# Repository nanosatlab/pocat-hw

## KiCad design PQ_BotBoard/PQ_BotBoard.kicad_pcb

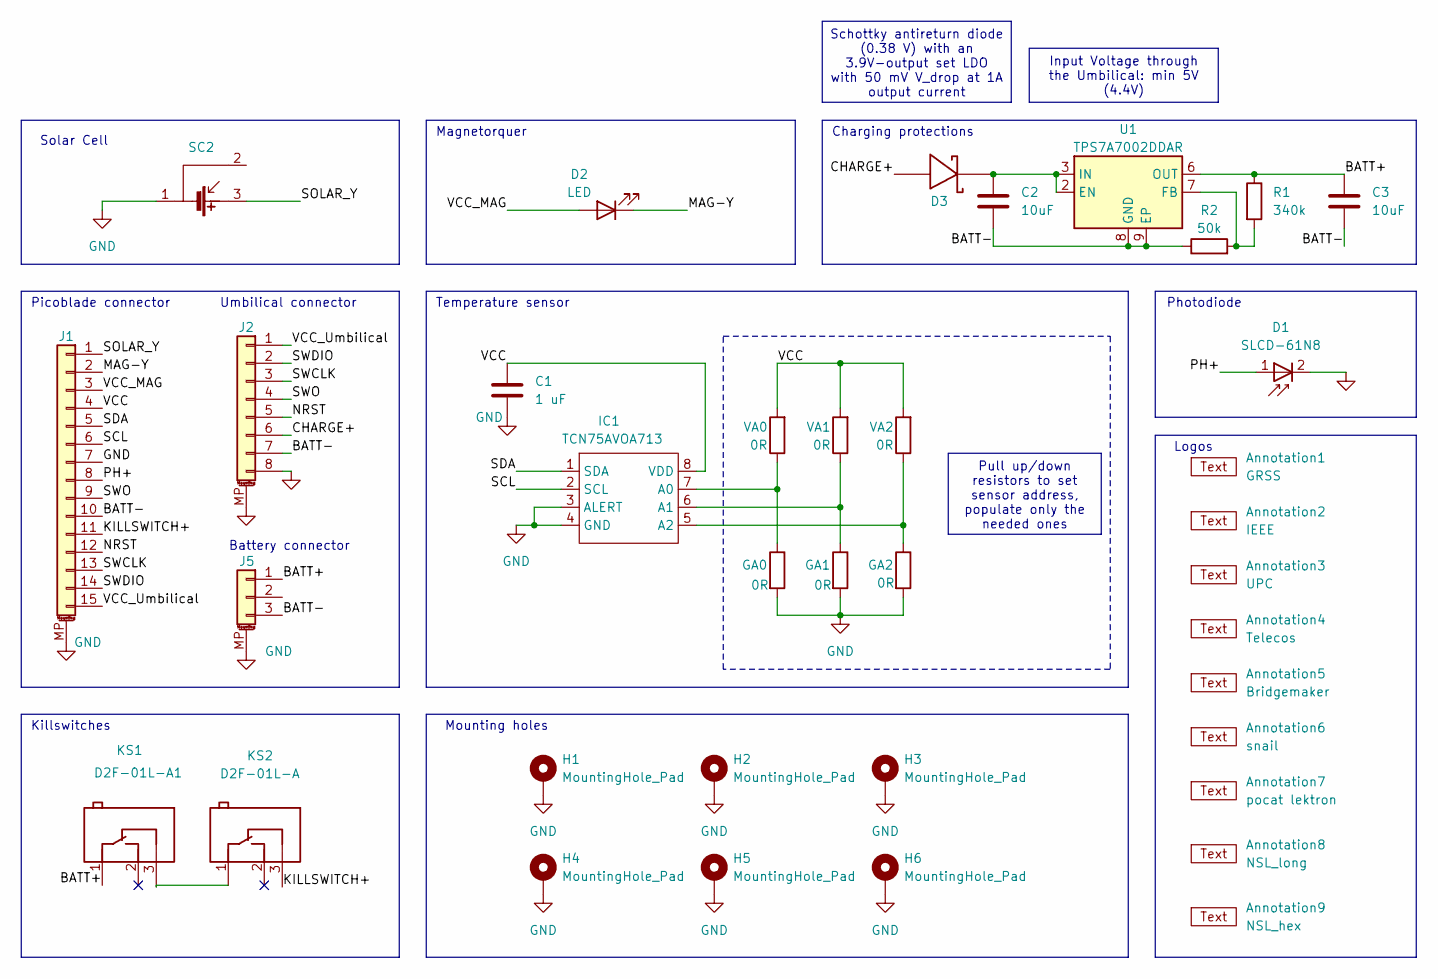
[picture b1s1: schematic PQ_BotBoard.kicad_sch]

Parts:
Annotation1: GRSS
Annotation2: IEEE; IEEE_logo
Annotation3: UPC; UPC_positiu
Annotation4: Telecos
Annotation5: Bridgemaker
Annotation6: snail; Snail
Annotation7: pocat lektron; pocat-lektron
Annotation8: NSL_long; NSL-small
Annotation9: NSL_hex; NSL_hexagon
C1: 1 uF; C_0603_1608Metric; Manufacturer Part Numbe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 GRM188R72A104KA35J
C2, C3: 10uF; C_0603_1608Metric
D1: SLCD-61N8; Manufacturer Part Numbe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 SLCD-61N8
D2: LED; LED_0402_1005Metric
D3: RBS1LAM40ATR_Schottky
GA0, GA1, GA2: 0R; R_0805_2012Metric; Manufacturer Part Numbe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 CRCW08055K00JNTA
H1, H2, H3, H4, H5, H6: MountingHole_Pad; MountingHole_2.2mm_M2_Pad; Manufacturer Part Numbe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 N/A
IC1: TCN75AVOA713; TCN75AVOA; Manufacturer Part Numbe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 TCN75AVOA
J1: 53261-1471; Molex_PicoBlade_53261-1571_1x15-1MP_P1.25mm_Horizontal; Manufacturer Part Numbe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 PicoBlade_53261-1571
J2: Conn_01x08_MountingPin; Molex_PicoBlade_53398-0871_1x08-1MP_P1.25mm_Vertical; Manufacturer Part Numbe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 PicoBlade_53398-0871
J5: Conn_01x03_MountingPin; Molex_PicoBlade_53261-0371_1x03-1MP_P1.25mm_Horizontal
KS1: D2F-01L-A1; D2FLA1; Manufacturer Part Numbe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 D2F-01L
KS2: D2F-01L-A; D2FLA; Manufacturer Part Numbe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 D2F-01L-A
R1: 340k; R_0603_1608Metric
R2: 50k; R_0603_1608Metric
SC2: Lighttricity_S3040_CIC
U1: TPS7A7002DDAR; TI_SO-PowerPAD-8
VA0, VA1, VA2: 0R; R_0805_2012Metric; Manufacturer Part Numbe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 CRCW08055K00JNTA

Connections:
/BATT+: C3.1, J5.1, KS1.1 (COM), R1.1, U1.6 (OUT)
/BATT-: C2.2, C3.2, J1.10, J2.7, J5.3, R2.1, U1.8 (GND), U1.9 (EP)
/CHARGE+: D3.2, J2.6
/KILLSWITCH+: J1.11, KS2.3 (NC)
/MAG-Y: D2.1 (K), J1.2
/NRST: J1.12, J2.5
/PH+: D1.1, J1.8
/SCL: IC1.2 (SCL), J1.6
/SDA: IC1.1 (SDA), J1.5
/SOLAR_Y: J1.1, SC2.3
/SWCLK: J1.13, J2.3
/SWDIO: J1.14, J2.2
/SWO: J1.9, J2.4
/VCC: C1.1, IC1.8 (VDD), J1.4, VA0.2, VA1.2, VA2.2
/VCC_MAG: D2.2 (A), J1.3
/VCC_Umbilical: J1.15, J2.1
GND: C1.2, D1.2, GA0.2, GA1.2, GA2.2, H1.1, H2.1, H3.1, H4.1, H5.1, H6.1, IC1.3 (ALERT), IC1.4 (GND), J1.7, J1.MP (MountPin), J2.8, J2.MP (MountPin), J5.MP (MountPin), SC2.1
unnamed: GA0.1, IC1.7 (A0), VA0.1
unnamed: GA1.1, IC1.6 (A1), VA1.1
unnamed: GA2.1, IC1.5 (A2), VA2.1
unnamed: KS1.3 (NC), KS2.1 (COM)
unnamed: C2.1, D3.1, U1.2 (EN), U1.3 (IN)
unnamed: R1.2, R2.2, U1.7 (FB)

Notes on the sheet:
Input Voltage through the Umbilical: min 5V (4.4V)
Schottky antireturn diode (0.38 V) with an 3.9V-output set LDO with 50 mV V_drop at 1A output current
Pull up/down resistors to set sensor address, populate only the needed ones
Temperature sensor
Killswitches
Mounting holes
Solar Cell
Magnetorquer
Charging protections
Photodiode
Umbilical connector
Battery connector
Picoblade connector
Logos

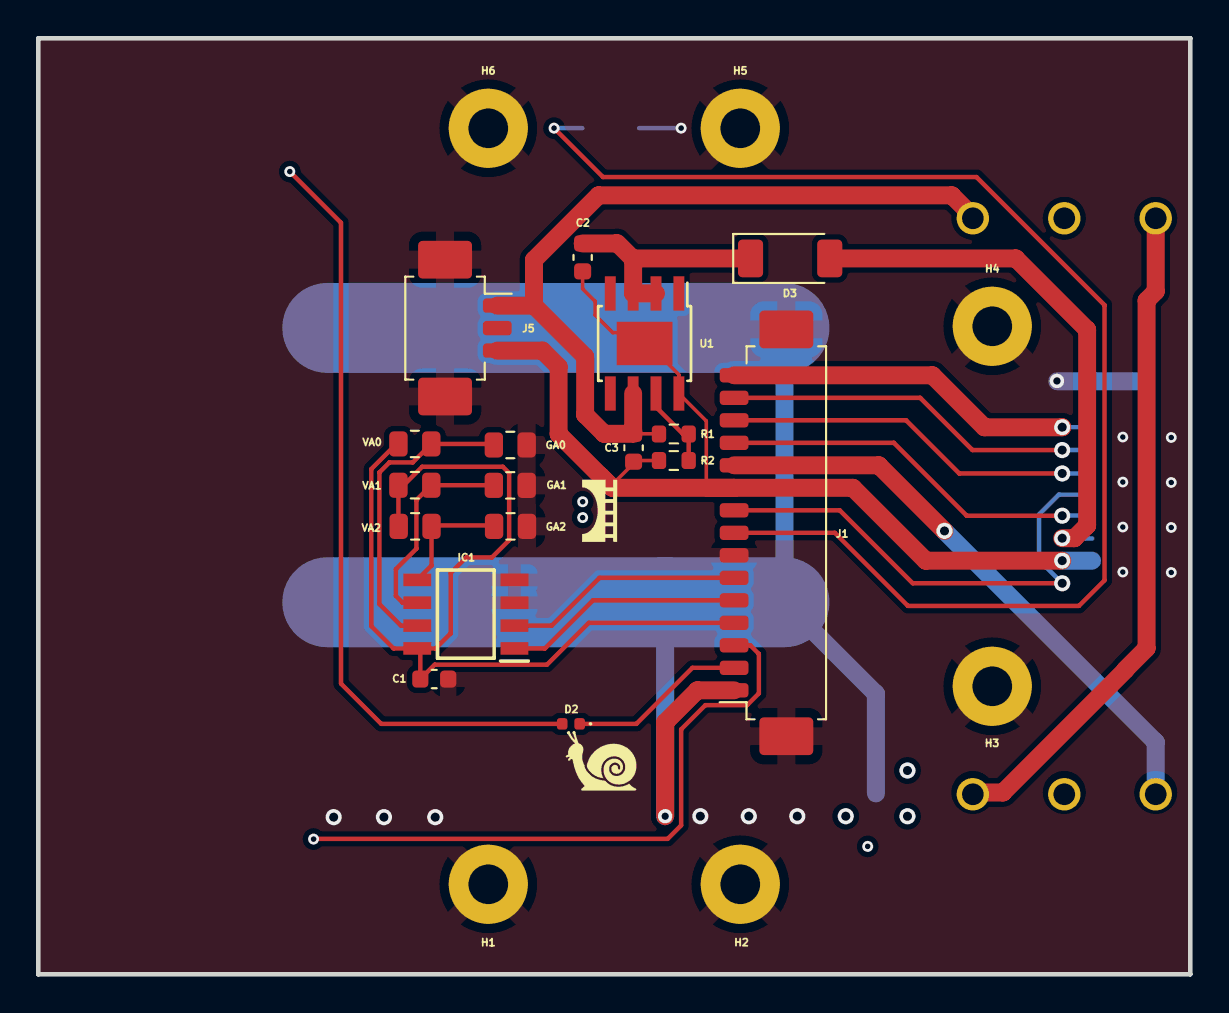
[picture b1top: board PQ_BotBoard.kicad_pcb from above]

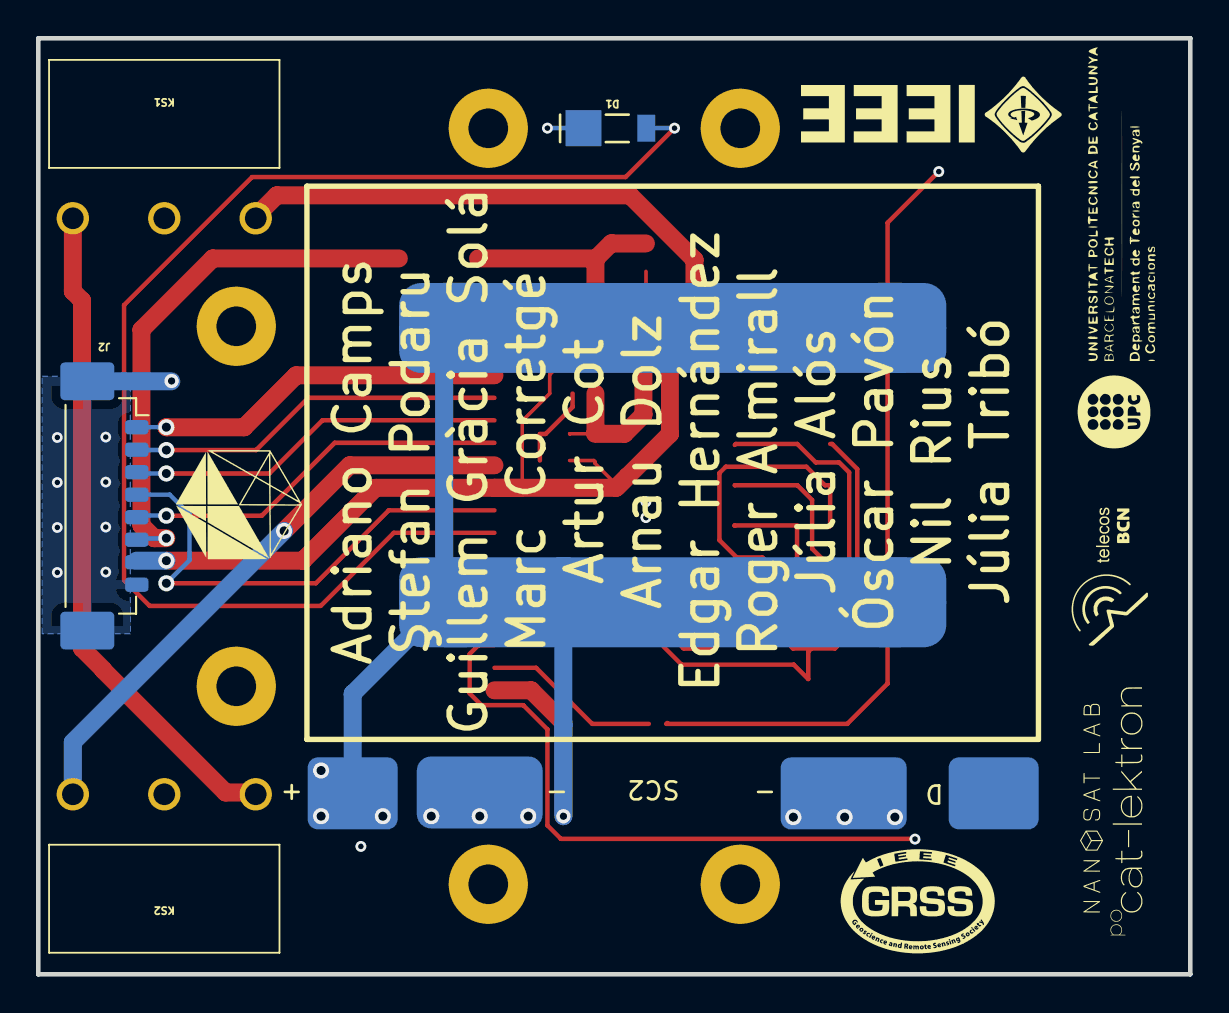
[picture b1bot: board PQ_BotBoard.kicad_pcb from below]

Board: 6 copper layers, 64.0 x 52.0 mm, 37 parts (12 on the bottom side), 23 nets.

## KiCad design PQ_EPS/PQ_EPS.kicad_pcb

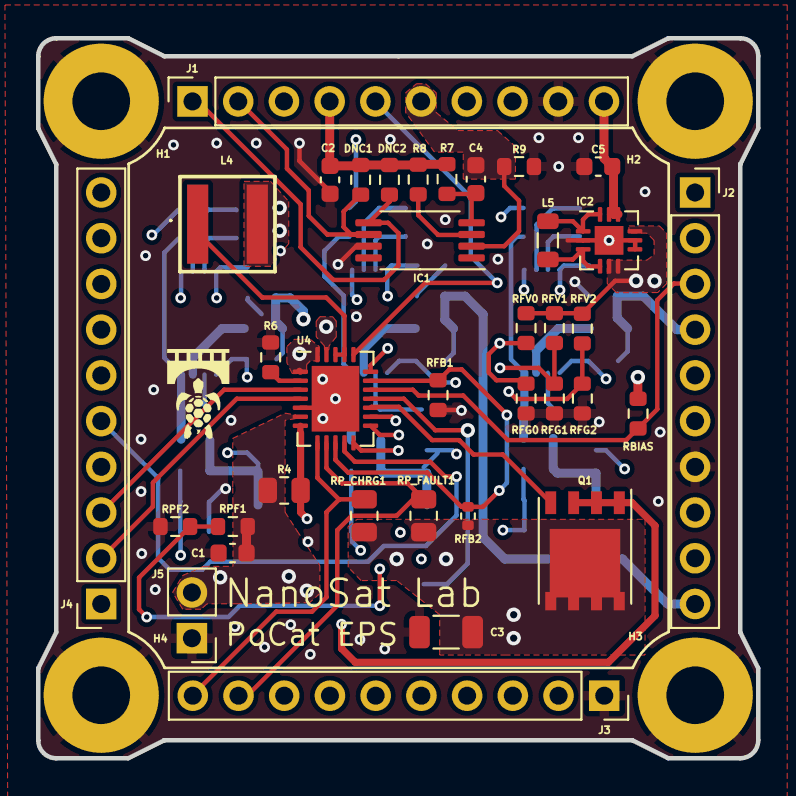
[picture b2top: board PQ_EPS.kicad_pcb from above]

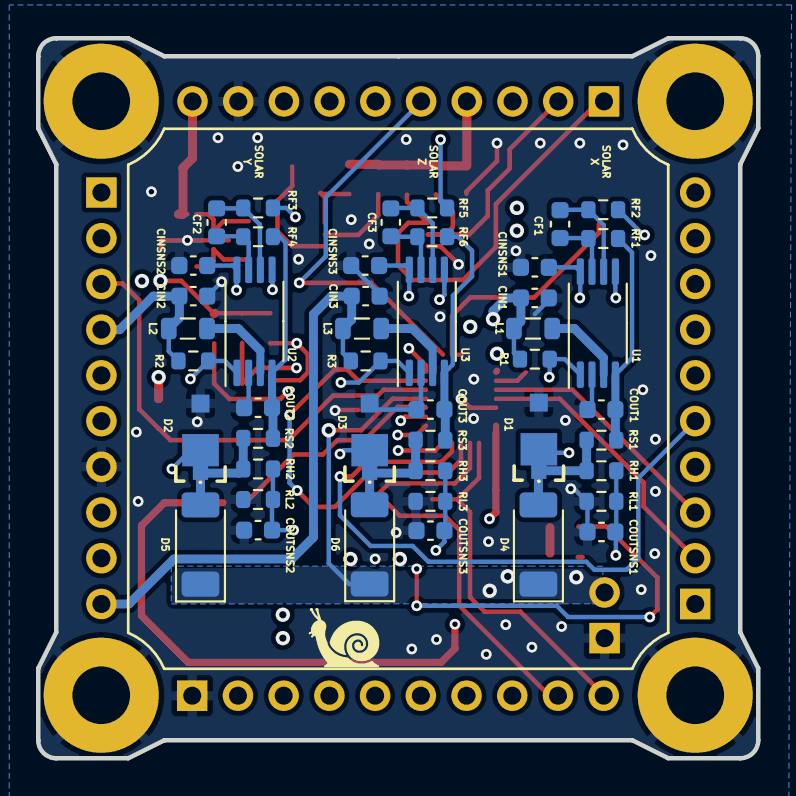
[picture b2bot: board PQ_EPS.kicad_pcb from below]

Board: 4 copper layers, 40.0 x 40.0 mm, 88 parts (46 on the bottom side), 52 nets.

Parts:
Annotation1: Silkscreen_Annotation; Bridgemaker
Annotation2: Silkscreen_Annotation; NakNak
Annotation3: Silkscreen_Annotation; Snail
C1: 2.2u; C_0603_1608Metric
C2: 10u; C_0603_1608Metric
C3: 100u; C_1206_3216Metric
C4: 0.1u; C_0603_1608Metric
C5: 22u; C_0603_1608Metric
CF1, CF2, CF3: 1u; C_0603_1608Metric
CIN1, CIN2, CIN3: 1.5u; C_0603_1608Metric
CINSNS1, CINSNS2, CINSNS3: 1n; C_0603_1608Metric
COUT1, COUT2, COUT3: 10u; C_0603_1608Metric
COUTSNS1, COUTSNS2, COUTSNS3: 1n; C_0603_1608Metric
D1, D2, D3: SMM4F; SMM4F15ATR
D4, D5, D6: shottky; RBS1LAM40ATR_Schottky
DNC1, DNC2: 20k; R_0603_1608Metric
H1, H2, H3, H4: MountingHole_Pad; MountingHole_3.2mm_M3_Pad
IC1: DS2782E+; TSSOP-8_4.4x3mm_P0.65mm
IC2: ISL9120IRTNZ
J1, J2, J3, J4: CES-110-02-L-S; SLW-110-01
J5: CES-102-02
L1, L2, L3: 10u; L_0805_2012Metric
L4: 2.2u; XAL5030222MEC
L5: 1u; L_0805_2012Metric
Q1: SIR424DP
R1, R2, R3, R8: 1k; R_0603_1608Metric
R4: 75m; R_0805_2012Metric
R6: 2k; R_0603_1608Metric
R7: 510; R_0603_1608Metric
R9: 15m; R_0603_1608Metric
RBIAS1: 10k; R_0603_1608Metric
RF1, RF2, RF3, RF4, RF5, RF6: 1k; R_0603_1608Metric
RFB1: 68k; R_0603_1608Metric
RFB2: 255k; R_0402_1005Metric
RFG0, RFG1, RFG2: 1k; R_0603_1608Metric
RFV0, RFV1, RFV2: 1k; R_0603_1608Metric
RH1, RH2, RH3: 910k; R_0603_1608Metric
RL1, RL2, RL3: 360k; R_0603_1608Metric
RPF1: 147k; R_0603_1608Metric
RPF2: 68k; R_0603_1608Metric
RP_CHRG1: 5k; R_0805_2012Metric
RP_FAULT1: 5k; R_0805_2012Metric
RS1, RS2, RS3: 300m; R_0603_1608Metric
U1, U2, U3: SPV1040TTR; TSSOP-8_4.4x3mm_P0.65mm
U4: LTC4040EUFD#PBF; QFN-24-1EP_4x5mm_P0.5mm_EP2.65x3.65mm

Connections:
3V3_PERM: C5.2, IC2.10 (FB), IC2.11 (VOUT), J1.10, RBIAS1.2
/F0: RFG0.1, RFV0.2, U4.14 (F0)
/F1: RFG1.1, RFV1.2, U4.13 (F1)
/F2: RFG2.1, RFV2.2, U4.12 (F2)
/PROG: R6.2, U4.2 (PROG)
BATT-: C4.2, IC1.2 (VSS), J1.6, R9.1
BATT_NTC: J2.3, RBIAS1.1, U4.17 (NTC)
CHOUT: C3.1, IC2.5 (VIN_1), IC2.6 (VIN_2), IC2.9 (EN), Q1.5 (D), RFB2.2, RFV0.1, RFV1.1, RFV2.1, RP_CHRG1.1, RP_FAULT1.1, U4.1 (VSYS), U4.24 (VSYS)
CHRG: J3.10, RP_CHRG1.2, U4.8 (CHRG#)
CHRGOFF: J4.2, U4.4 (CHGOFF)
CLPROG: J4.3, U4.3 (CLPROG)
FAULT: J3.9, RP_FAULT1.2, U4.9 (FAULT#)
GND: C1.2, C2.2, C3.2, C5.1, CIN1.1, CIN2.1, CIN3.1, CINSNS1.1, CINSNS2.1, CINSNS3.1, COUT1.1, COUT2.1, COUT3.1, COUTSNS1.1, COUTSNS2.1, COUTSNS3.1, D1.2, D2.2, D3.2, H1.1, H2.1, H3.1, H4.1, IC1.7 (SNS), IC2.2 (PGND), IC2.7 (BYPS), IC2.8 (GND), IC2.13 (EP), J1.9, J2.7, J3.1, J5.1, R6.1, R9.2, RFB1.2, RFG0.2, RFG1.2, RFG2.2, RL1.2, RL2.2, RL3.2, RPF2.1, U1.2 (GND), U2.2 (GND), U3.2 (GND), U4.5 (BSTOFF), U4.25 (EPAD)
KILLSWITCH+: C2.1, DNC1.2, DNC2.2, J1.4, L4.2, R7.2, R8.2, U4.23 (BAT)
NRST: J4.5, U4.11 (RST#)
unnamed: D1.1, D4.2, RF2.2, RH1.1, RS1.2
unnamed: D2.1, D5.2, RF3.2, RH2.1, RS2.2
unnamed: D3.1, D6.2, RF5.2, RH3.1, RS3.2
unnamed: C4.1, IC1.4 (VDD), R7.1
unnamed: IC1.3 (VIN), R8.1
unnamed: IC2.3 (LX1_1), IC2.4 (LX1_2), L5.1
unnamed: IC2.1 (LX2_1), IC2.12 (LX2_2), L5.2
unnamed: L4.1, U4.21 (SW), U4.22 (SW)
unnamed: Q1.4 (G), U4.15 (IGATE)
unnamed: CF1.1, RF2.1, U1.6 (ICTRL-MINUS)
unnamed: CF1.2, RF1.1, U1.7 (ICTRL-PLUS)
unnamed: L1.1, U1.3 (LX)
unnamed: CINSNS1.2, R1.1, U1.1 (MPP-SET), U1.8 (XSHUT)
unnamed: COUTSNS1.2, RH1.2, RL1.1, U1.5 (VCTRL)
unnamed: COUT1.2, RF1.2, RS1.1, U1.4 (VOUT)
unnamed: CF2.1, RF3.1, U2.6 (ICTRL-MINUS)
unnamed: CF2.2, RF4.1, U2.7 (ICTRL-PLUS)
unnamed: L2.2, U2.3 (LX)
unnamed: CINSNS2.2, R2.1, U2.1 (MPP-SET), U2.8 (XSHUT)
unnamed: COUTSNS2.2, RH2.2, RL2.1, U2.5 (VCTRL)
unnamed: COUT2.2, RF4.2, RS2.1, U2.4 (VOUT)
unnamed: CF3.1, RF5.1, U3.6 (ICTRL-MINUS)
unnamed: CF3.2, RF6.1, U3.7 (ICTRL-PLUS)
unnamed: L3.2, U3.3 (LX)
unnamed: CINSNS3.2, R3.1, U3.1 (MPP-SET), U3.8 (XSHUT)
unnamed: COUTSNS3.2, RH3.2, RL3.1, U3.5 (VCTRL)
unnamed: COUT3.2, RF6.2, RS3.1, U3.4 (VOUT)
unnamed: RFB1.1, RFB2.1, U4.10 (RSTFB), U4.18 (BSTFB)
unnamed: Q1.1 (S), Q1.2 (S), Q1.3 (S), R4.2, U4.7 (CLN)
unnamed: RPF1.1, RPF2.2, U4.19 (PFI)
OVSNS: C1.1, D4.1, D5.1, D6.1, J5.2, R4.1, RPF1.2, U4.6 (VIN), U4.16 (OVSNS)
PFO: J1.5, U4.20 (PF0#)
SCL1: DNC1.1, IC1.6 (SCL), J1.2
SDA1: DNC2.1, IC1.5 (SDA), J1.1
SOLAR_X: CIN1.2, J4.1, L1.2, R1.2
SOLAR_Y: CIN2.2, J2.4, L2.1, R2.2
SOLAR_Z: CIN3.2, J2.10, L3.1, R3.2

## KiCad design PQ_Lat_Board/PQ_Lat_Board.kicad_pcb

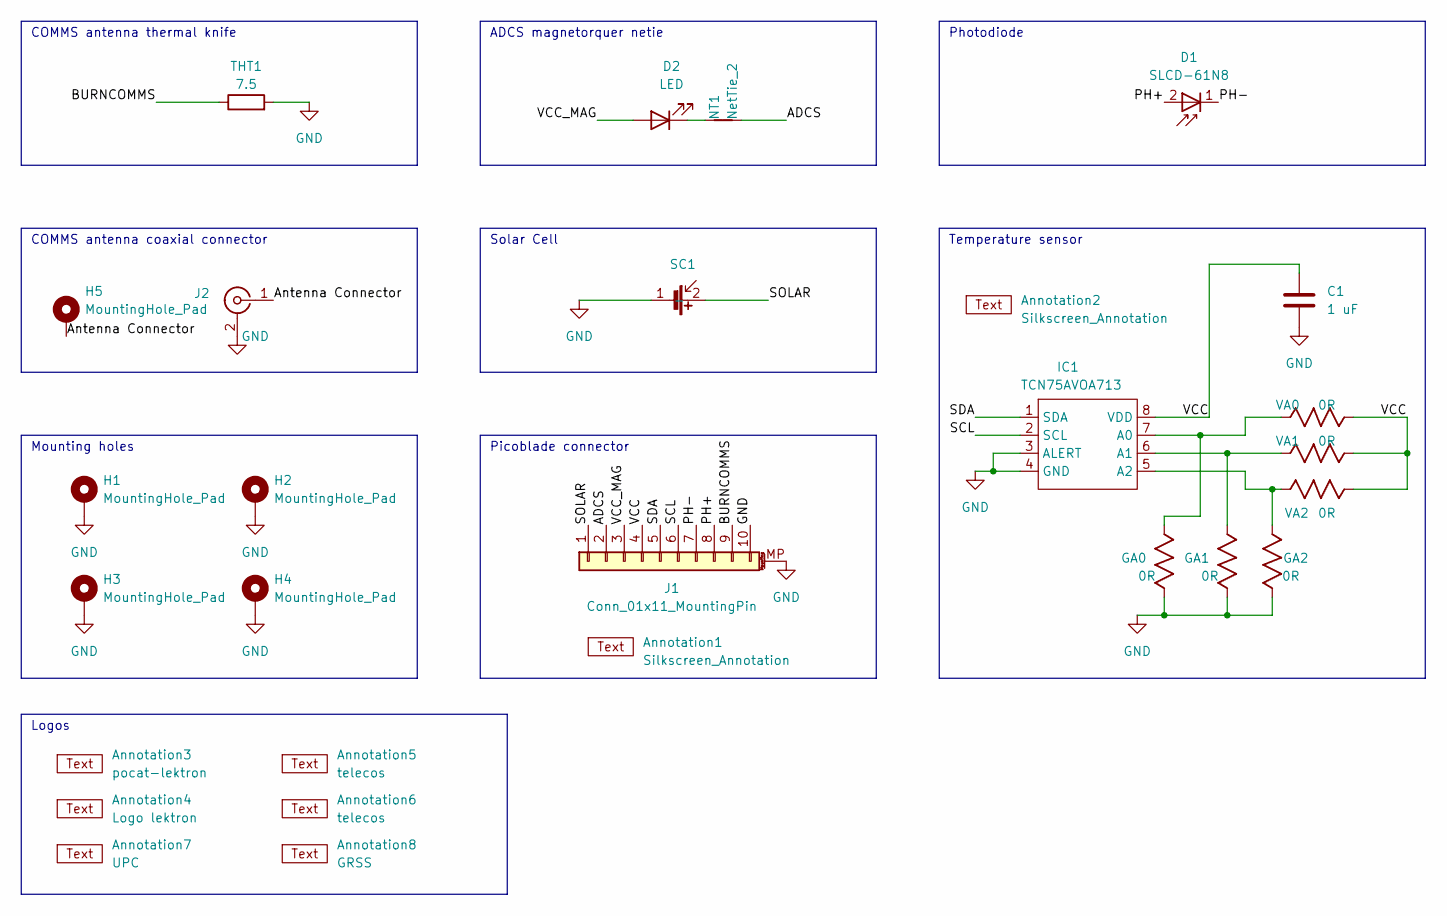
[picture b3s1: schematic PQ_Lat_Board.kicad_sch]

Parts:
Annotation1: Silkscreen_Annotation; Bridgemaker
Annotation2: Silkscreen_Annotation; snail
Annotation3: pocat-lektron
Annotation4: Logo lektron; logo_pq
Annotation5: telecos; Telecos
Annotation6: telecos; NSL-small
Annotation7: UPC; UPC_small
Annotation8: GRSS
C1: 1 uF; C_0603_1608Metric; Manufacturer Part Numbe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 GRM188R72A104KA35J
D1: SLCD-61N8; Manufacturer Part Numbe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 SLCD-61N8
D2: LED; LED_0402_1005Metric
GA0, GA1, GA2: 0R; R_0805_2012Metric; Manufacturer Part Numbe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 CRCW08055K00JNTA
H1, H2, H3, H4: MountingHole_Pad; MountingHole_2.2mm_M2_Pad; Manufacturer Part Numbe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 N/A
H5: MountingHole_Pad; MountingHole_2.2mm_M2_DIN965_Pad_TopOnly; Manufacturer Part Numbe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 N/A
IC1: TCN75AVOA713; TCN75AVOA; Manufacturer Part Numbe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 TCN75AVOA
J1: Conn_01x11_MountingPin; Molex_PicoBlade_53261-1071_1x10-1MP_P1.25mm_Horizontal; Manufacturer Part Numbe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 PicoBlade_53261
J2: Conn_Coaxial; U.FL_Hirose_U.FL-R-SMT-1_Vertical
NT1: NetTie_2; NetTie-2_SMD_Pad0.5mm; Manufacturer Part Numbe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 N/A
SC1: Lighttricity_S3040_CIC
THT1: 7.5; R_Axial_DIN0309_L9.0mm_D3.2mm_P12.70mm_Horizontal; Manufacturer Part Numbe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 MRS25000C7508FCT00
VA0, VA1, VA2: 0R; R_0805_2012Metric; Manufacturer Part Numbe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 CRCW08055K00JNTA

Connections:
/ADCS: J1.2, NT1.2
/Antenna Connector: H5.1, J2.1 (In)
/BURNCOMMS: J1.9, THT1.1
/PH+: D1.2, J1.8
/PH-: D1.1, J1.7
/SCL: IC1.2 (SCL), J1.6
/SDA: IC1.1 (SDA), J1.5
/SOLAR: J1.1, SC1.2
/VCC: C1.1, IC1.8 (VDD), J1.4, VA0.2, VA1.2, VA2.2
/VCC_MAG: D2.2 (A), J1.3
GND: C1.2, GA0.1, GA1.1, GA2.1, H1.1, H2.1, H3.1, H4.1, IC1.3 (ALERT), IC1.4 (GND), J1.10, J1.MP (MountPin), J2.2 (Ext), SC1.1 (-), THT1.2
unnamed: D2.1 (K), NT1.1
unnamed: GA0.2, IC1.7 (A0), VA0.1
unnamed: GA1.2, IC1.6 (A1), VA1.1
unnamed: GA2.2, IC1.5 (A2), VA2.1

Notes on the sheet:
COMMS antenna thermal knife
Temperature sensor
Mounting holes
COMMS antenna coaxial connector
Solar Cell
Logos
Photodiode
ADCS magnetorquer netie
Picoblade connector

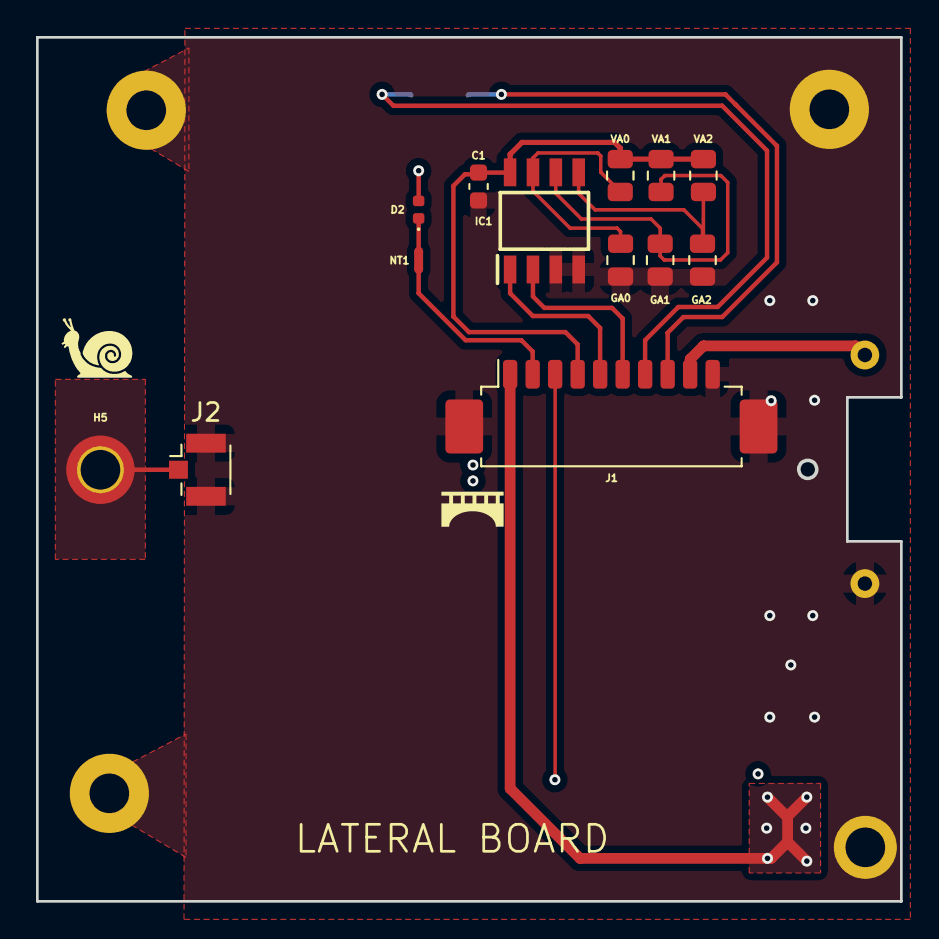
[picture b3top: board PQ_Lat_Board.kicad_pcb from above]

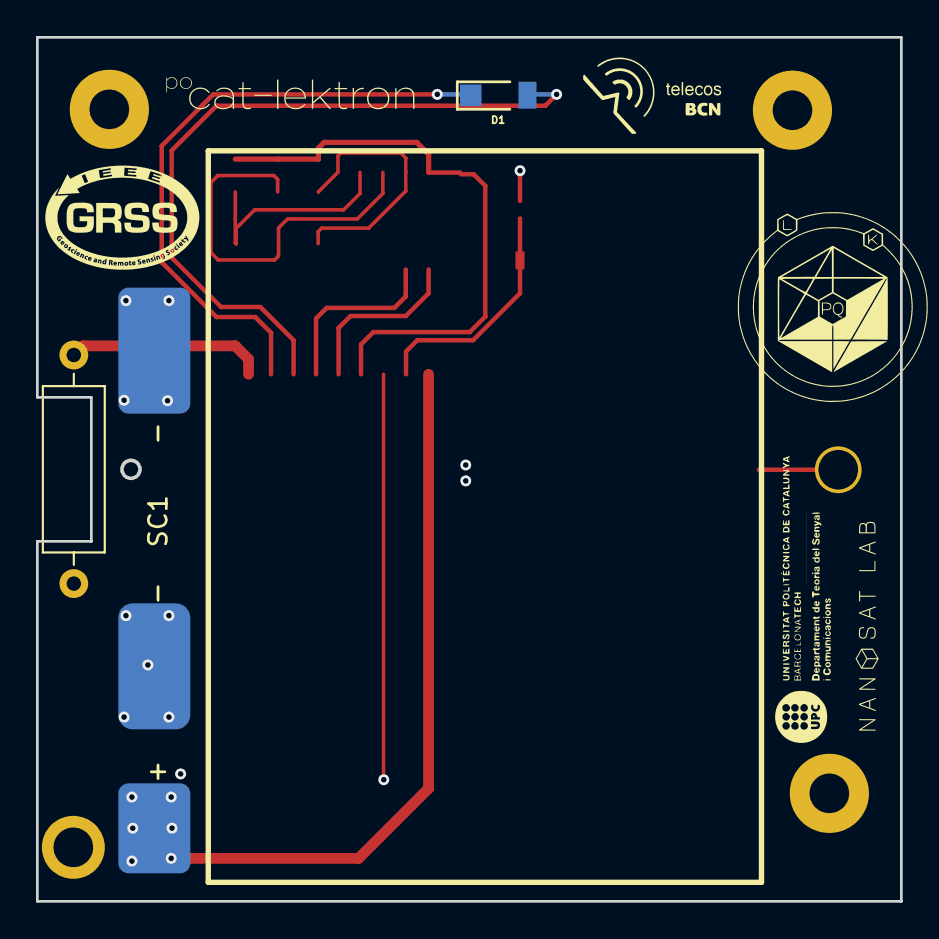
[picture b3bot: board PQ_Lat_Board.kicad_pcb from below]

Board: 6 copper layers, 48.0 x 48.0 mm, 28 parts (9 on the bottom side), 15 nets.

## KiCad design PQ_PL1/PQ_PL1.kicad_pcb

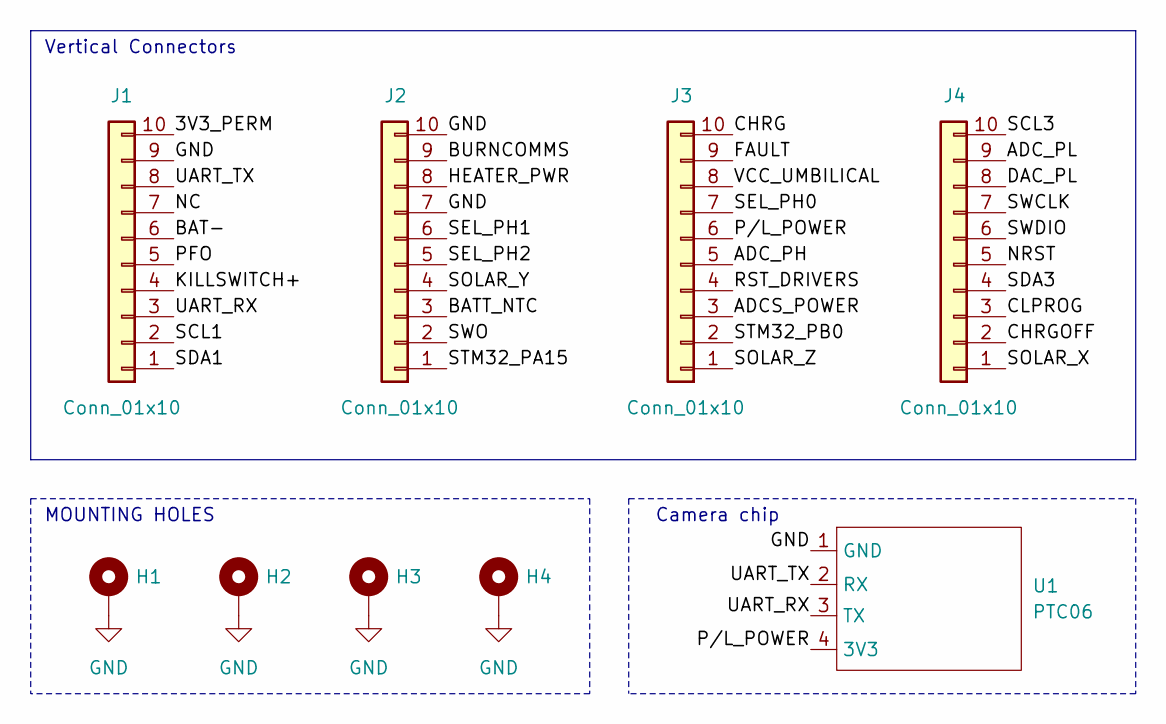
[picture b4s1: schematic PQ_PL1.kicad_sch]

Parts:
H1, H2, H3, H4: MountingHole_Pad; MountingHole_3.2mm_M3_Pad
J1, J2, J3, J4: Conn_01x10; BBL-110-Y-X
U1: PTC06

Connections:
/3V3_PERM: J1.10
/ADCS_POWER: J3.3
/ADC_PH: J3.5
/ADC_PL: J4.9
/BAT-: J1.6
/BATT_NTC: J2.3
/BURNCOMMS: J2.9
/CHRG: J3.10
/CHRGOFF: J4.2
/CLPROG: J4.3
/DAC_PL: J4.8
/FAULT: J3.9
/HEATER_PWR: J2.8
/KILLSWITCH+: J1.4
/NC: J1.7
/NRST: J4.5
/PFO: J1.5
/P/L_POWER: J3.6, U1.4 (3V3)
/RST_DRIVERS: J3.4
/SCL1: J1.2
/SCL3: J4.10
/SDA1: J1.1
/SDA3: J4.4
/SEL_PH0: J3.7
/SEL_PH1: J2.6
/SEL_PH2: J2.5
/SOLAR_X: J4.1
/SOLAR_Y: J2.4
/SOLAR_Z: J3.1
/STM32_PA15: J2.1
/STM32_PB0: J3.2
/SWCLK: J4.7
/SWDIO: J4.6
/SWO: J2.2
/UART_RX: J1.3, U1.3 (TX)
/UART_TX: J1.8, U1.2 (RX)
/VCC_UMBILICAL: J3.8
GND: H1.1, H2.1, H3.1, H4.1, J1.9, J2.7, J2.10, U1.1 (GND)

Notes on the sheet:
MOUNTING HOLES
Camera chip
Vertical Connectors

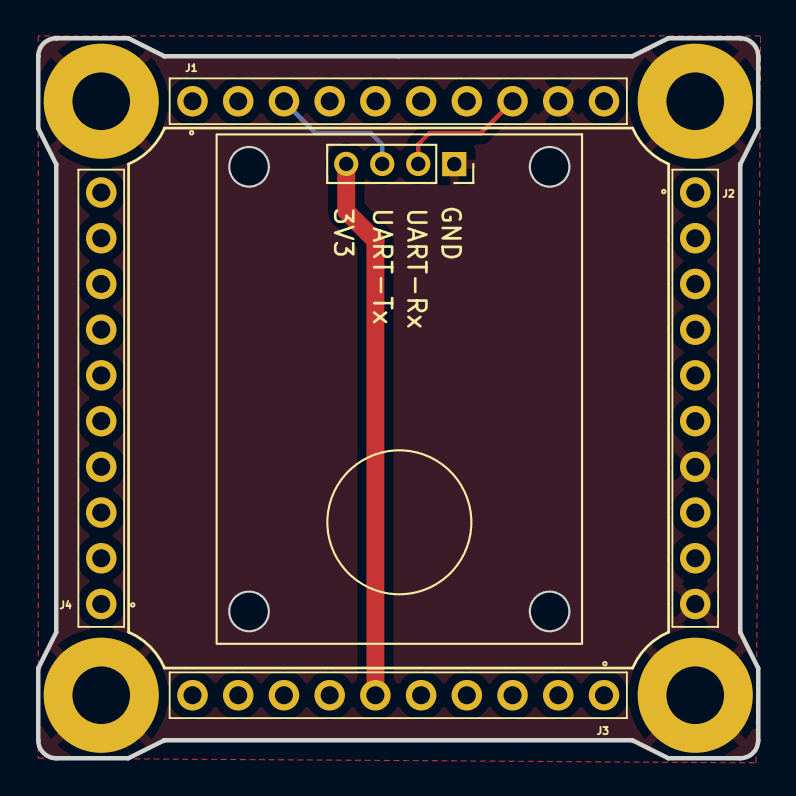
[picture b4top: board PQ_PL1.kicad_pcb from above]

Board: 2 copper layers, 40.0 x 40.0 mm, 9 parts (0 on the bottom side), 4 nets.

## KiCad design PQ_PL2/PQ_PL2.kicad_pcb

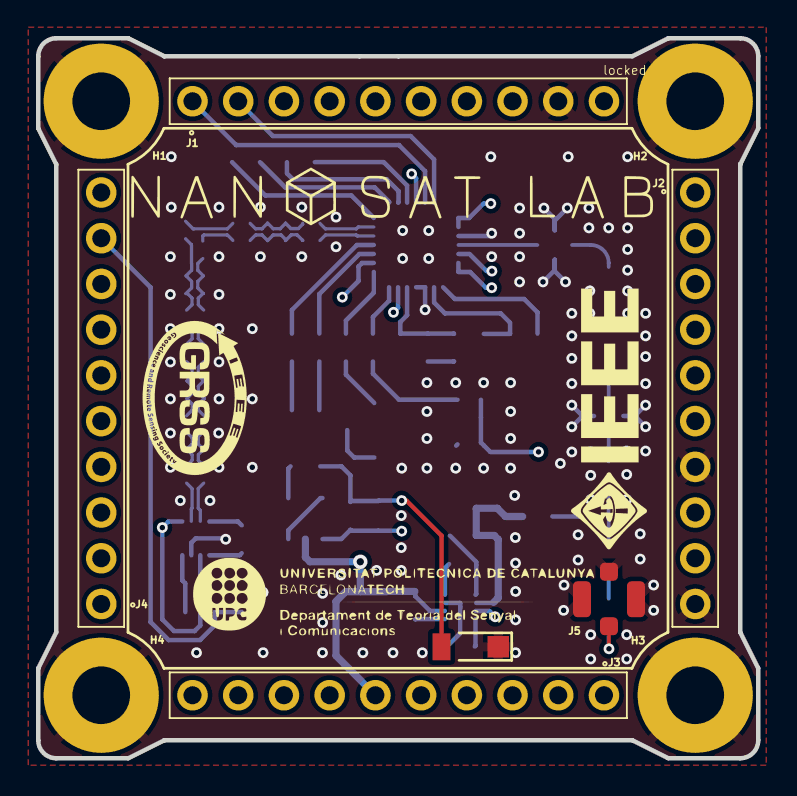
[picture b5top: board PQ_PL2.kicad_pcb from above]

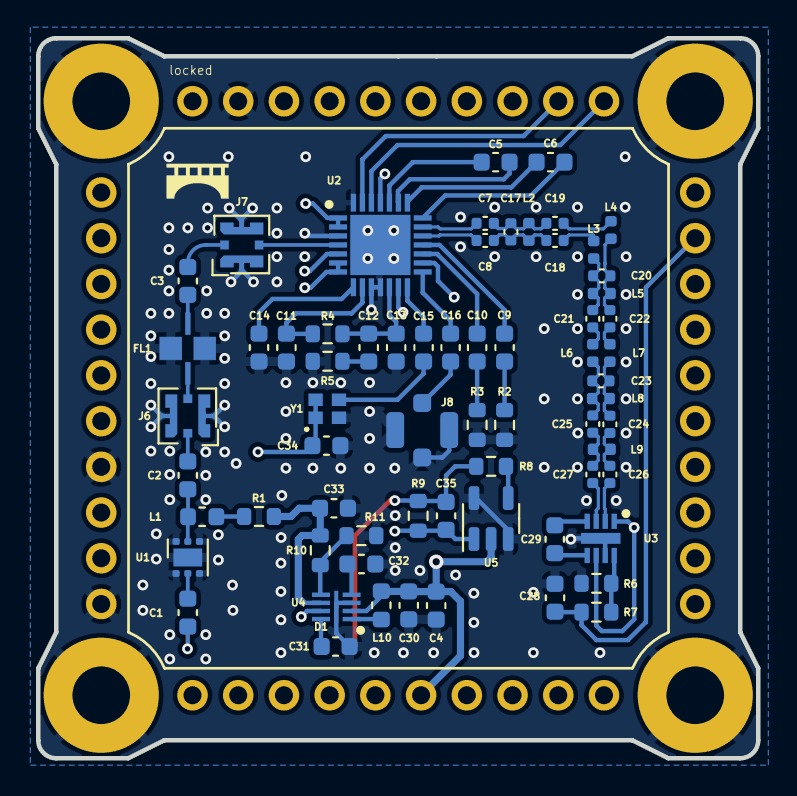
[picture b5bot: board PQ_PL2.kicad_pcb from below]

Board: 4 copper layers, 40.0 x 40.0 mm, 81 parts (67 on the bottom side), 58 nets.

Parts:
Annotation1: Silkscreen_Annotation; Bridgemaker
Annotation2: Silkscreen_Annotation; GRSS
Annotation3: Silkscreen_Annotation; NSL_long
Annotation4: Silkscreen_Annotation; IEEE_logo
Annotation5: Silkscreen_Annotation; UPC_positiu
C1, C2, C3, C4, C32: 1nF; C_0603_1608Metric
C5, C6, C9, C10, C14, C34: 47nF; C_0603_1608Metric
C7, C8: 47nF; C_0402_1005Metric
C11: 2.2pF; C_0603_1608Metric
C12: 270pF; C_0603_1608Metric
C13: 22pF; C_0603_1608Metric
C15, C16: 1.2nF; C_0603_1608Metric
C17, C23: 300pF; C_0402_1005Metric
C18, C19, C21, C22: 1.3pF; C_0402_1005Metric
C20: 500pF; C_0402_1005Metric
C24, C25: 12 pF; C_0402_1005Metric
C26, C27: 10nF; C_0402_1005Metric
C28: 27pF; C_0603_1608Metric
C29: 33nF; C_0603_1608Metric
C30, C33: 1uF; C_0603_1608Metric
C31: 4.7uF; C_0603_1608Metric
C35: 100 pF; C_0603_1608Metric
D1: SLCD-61N8
FL1: BFCG162W; GE0805C-3
H1, H2, H3, H4: MountingHole_Pad; MountingHole_3.2mm_M3_Pad
J1, J2, J3, J4: BBL-110-Y-X
J5, J8: U.FL-R-SMT; U.FL-R-SMT-1(10)
J6, J7: MS-156C3; CoaxialSwitch_Hirose_MS-156C3_Horizontal
L1: 100nH; L_0603_1608Metric
L2, L8: 16.4nH; L_0402_1005Metric
L3, L4, L6, L7: 3.9nH; L_0402_1005Metric
L5: 10.2nH; L_0402_1005Metric
L9: 680 nH; L_0402_1005Metric
L10: 4.7uH; L_0603_1608Metric
R1: 87.5; R_0603_1608Metric
R2, R3: 75; R_0603_1608Metric
R4, R11: 120k; R_0603_1608Metric
R5: 15k; R_0603_1608Metric
R6, R7: 33K; R_0603_1608Metric
R8: 100; R_0603_1608Metric
R9: 2k; R_0603_1608Metric
R10: 360k; R_0603_1608Metric
U1: LEE2-6+; WSON-6-1EP_2x2mm_P0.65mm_EP1x1.6mm
U2: MAX2121; QFN50P500X500X80-29N
U3: LT5537; SON50P200X300X80-9N-D
U4: LT3048; SON45P200X200X80-9N
U5: TL071; TSOT-23-5
Y1: ECS-TXO-2016MV; ECSTXO201633320TR

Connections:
5V: C33.2, R1.1, R10.2, U4.6 (LDOUT)
A+: C18.1, L3.2
A-: C19.1, L4.2
ADC_PL: C28.1, J4.9, R7.2
B+: C20.2, C21.2, L3.1, L5.1
B-: C20.1, C22.2, L4.1, L5.2
C+: C21.1, L6.2
C-: C22.1, L7.2
D+: C24.1, C26.2, L9.2
D-: C25.1, C27.2, L9.1
DAC_PL: J4.8, U2.5 (GC1)
E+: C26.1, U3.2 (IN+)
E-: C27.1, U3.3 (IN-)
GND: C4.2, C11.2, C13.2, C14.2, C28.2, C30.2, C31.1, C32.1, C33.1, C34.1, D1.2, FL1.2 (GND), FL1.4 (GND), H1.1, H2.1, H3.1, H4.1, J1.9, J2.7, J2.10, J5.2, J6.G, J7.G, J8.2, R2.2, R3.2, R5.2, R6.1, R11.1, U1.1 (NC), U1.3 (NC), U1.4 (NC), U1.6 (NC), U1.7 (GND), U2.3 (GND), U2.10 (GNDTUNE), U2.11 (GNDSYN), U2.28 (ADDR), U2.29 (EP), U3.7 (VEE), U3.9 (EPAD), U4.3 (GND1), U4.9 (GND2), U5.3 (+), U5.5 (V+), Y1.2 (GND)
IF+: C8.1, C17.2, C18.2, L2.1
IF-: C7.1, C17.1, C19.2, L2.2
IO+: C8.2, U2.19 (IOUT+)
IO-: C7.2, U2.20 (IOUT-)
unnamed: C1.1, J5.1
unnamed: C2.2, J6.I
unnamed: C9.1, R2.1
unnamed: C10.1, R3.1
unnamed: C12.2, R5.1
unnamed: C16.2, J8.1
unnamed: C35.2, D1.1, R8.2, R9.1
unnamed: FL1.1 (IN), J6.O
unnamed: C3.1, FL1.3 (Out)
unnamed: L1.1, R1.2
unnamed: C1.2, U1.2 (In)
unnamed: C2.1, L1.2, U1.5 (Out&DCin)
unnamed: C14.1, U2.8 (BYPVCO)
unnamed: C12.1, C13.1, R4.2, U2.12 (CPOUT)
unnamed: C6.1, U2.21 (IDC+)
unnamed: C6.2, U2.22 (IDC-)
unnamed: C5.1, U2.23 (QDC+)
unnamed: C5.2, U2.24 (QDC-)
unnamed: C10.2, U2.17 (QOUT+)
unnamed: C9.2, U2.18 (QOUT-)
unnamed: C16.1, U2.15 (REFOUT)
unnamed: J7.O, U2.4 (RFIN)
unnamed: C11.1, R4.1, U2.9 (TUNEVCO)
unnamed: C15.1, U2.14 (XTAL)
unnamed: C29.2, U3.4 (CAP+)
unnamed: C29.1, U3.5 (CAP-)
unnamed: R6.2, R7.1, U3.8 (OUT)
unnamed: C31.2, U4.8 (BSTOUT)
unnamed: C32.2, U4.4 (BYP)
unnamed: R10.1, R11.2, U4.5 (FB)
unnamed: L10.2, U4.1 (SW)
unnamed: R8.1, U5.4 (-)
unnamed: C15.2, Y1.3 (Out)
P/L_POWER: C4.1, C30.1, C34.2, J3.6, L10.1, U2.1 (VCC_RF1), U2.2 (VCC_RF2), U2.6 (VCC_LO), U2.7 (VCC_VCO), U2.13 (VCC_SYN), U2.16 (VCC_DIG), U2.25 (VCC_BB), U3.1 (ENBL), U3.6 (VCC), U4.2 (VIN), U4.7 (EN), U5.2 (V-), Y1.1 (Tri), Y1.4 (VDD)
RF: C3.2, J7.I
RSSI+: C23.2, C25.2, L6.1, L8.1
RSSI-: C23.1, C24.2, L7.1, L8.2
SCL1: J1.2, U2.27 (SCL)
SDA1: J1.1, U2.26 (SDA)
STM32_PB0: C35.1, J3.2, R9.2, U5.1
